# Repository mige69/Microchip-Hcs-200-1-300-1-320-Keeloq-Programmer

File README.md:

# Microchip-Hcs-200-1-300-1-320-Keeloq-Programmer

programmer keeloq hcs200/1 hcs300/1 hcs320
verified program saves hcs content on sd card
atmega644 tqfp
shield tft 2.4 mcufriends touchscreen
Keeloq simple normal secure

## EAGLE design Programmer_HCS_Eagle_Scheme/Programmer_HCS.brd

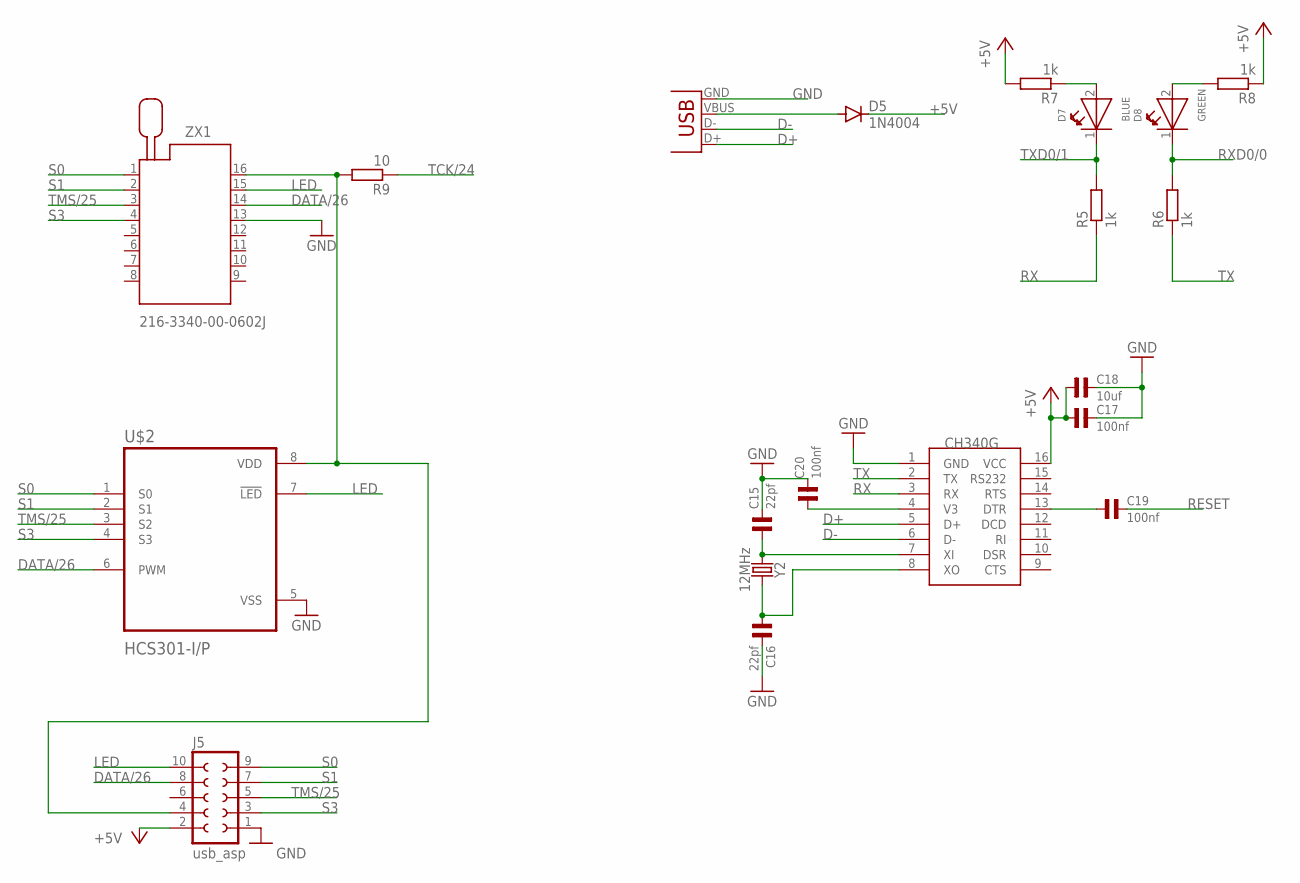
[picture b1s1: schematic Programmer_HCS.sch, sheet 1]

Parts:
C15, C16: 22pf; 0805
C17, C19, C20: 100nf; 0805
C18: 10uf; 0805
D5: 1N4004; DO214AA
D7: BLUE; 0805
D8: GREEN; 0805
J5: usb_asp; S10V
R5, R6, R7, R8: 1k; R0805
R9: 10; R0805
U$1: CH340G; SOIC16
U$2: HCS301-I/P; DIP787W46P254L927H533Q8
X1: USB-B-H
Y2: 12MHz; HC49US
ZX1: 216-3340-00-0602J

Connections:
+5V: C17.1, C18.1, D5.C, J5.2, R7.2, R8.1, U$1.16 (VCC); also elsewhere on the board
D+: U$1.5 (D+), X1.D+
D-: U$1.6 (D-), X1.D-
DATA/26: J5.8, U$2.6 (PWM), ZX1.14; also elsewhere on the board
GND: C15.2, C16.2, C17.2, C18.2, C20.2, J5.1, U$1.1 (GND), U$2.5 (VSS), X1.GND, ZX1.13; also elsewhere on the board
LED: J5.10, U$2.7 (!LED), ZX1.15
unnamed: C15.1, U$1.7 (XI), Y2.1
unnamed: C16.1, U$1.8 (XO), Y2.2
unnamed: D8.2 (A), R8.2
unnamed: D5.A, X1.VBUS
unnamed: C19.1, U$1.13 (DTR)
unnamed: D7.2 (A), R7.1
unnamed: C20.1, U$1.4 (V3)
unnamed: J5.4, R9.2, U$2.8 (VDD), ZX1.16
RESET: C19.2; also elsewhere on the board
RX: R5.1, U$1.3 (RX)
RXD0/0: D8.1 (K), R6.2; also elsewhere on the board
S0: J5.9, U$2.1 (S0), ZX1.1
S1: J5.7, U$2.2 (S1), ZX1.2
S3: J5.3, U$2.4 (S3), ZX1.4
TCK/24: R9.1; also elsewhere on the board
TMS/25: J5.5, U$2.3 (S2), ZX1.3; also elsewhere on the board
TX: R6.1, U$1.2 (TX)
TXD0/1: D7.1 (K), R5.2; also elsewhere on the board

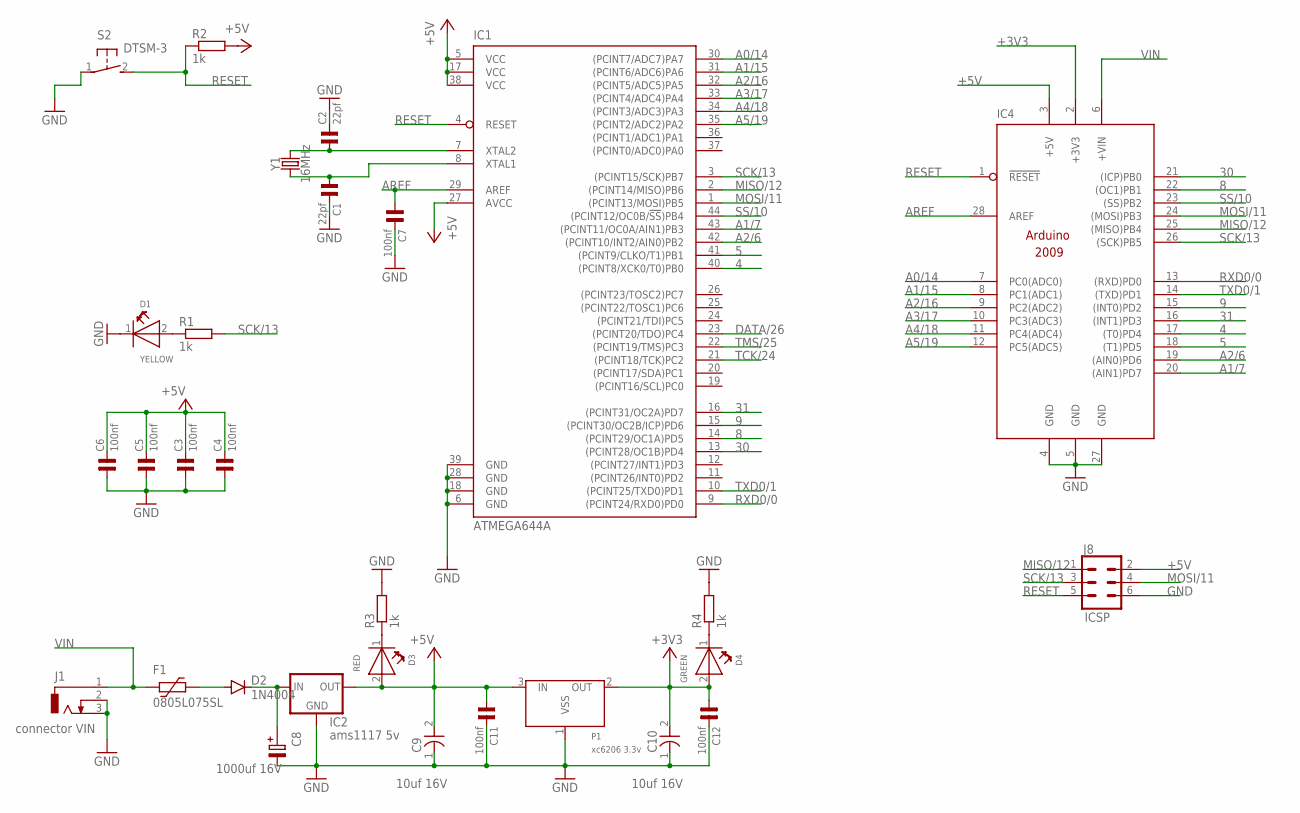
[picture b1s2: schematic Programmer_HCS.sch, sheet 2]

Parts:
C1, C2: 22pf; 0805
C3, C4, C5, C6, C7, C11, C12: 100nf; 0805
C8: 1000uf 16V; SV-G
C9, C10: 10uf 16V; 6032
D1: YELLOW; 3528-2PIN
D2: 1N4004; DO-214AC
D3: RED; 3528-2PIN
D4: GREEN; 3528-2PIN
F1: 0805L075SL; 0805L
IC1: ATMEGA644A; TQFP44
IC2: ams1117 5v; SOT223
IC4: UNO; ARDUINO2009
J1: connector VIN; DCJ0303
J8: ICSP; 2X3
P1: xc6206 3.3v; XC6206_SOT-23
R1, R2, R3, R4: 1k; R0805
S2: DTSM-3
Y1: 16MHz; HC49US

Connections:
4: IC1.40 ((PCINT8/XCK0/T0)PB0), IC4.17 ((T0)PD4)
5: IC1.41 ((PCINT9/CLKO/T1)PB1), IC4.18 ((T1)PD5)
8: IC1.14 ((PCINT29/OC1A)PD5), IC4.22 ((OC1)PB1)
9: IC1.15 ((PCINT30/OC2B/ICP)PD6), IC4.15 ((INT0)PD2)
30: IC1.13 ((PCINT28/OC1B)PD4), IC4.21 ((ICP)PB0)
31: IC1.16 ((PCINT31/OC2A)PD7), IC4.16 ((INT1)PD3)
+3V3: C10.2 (+), C12.1, D4.2 (A), IC4.2 (+3V3), P1.2 (OUT)
+5V: C3.2, C4.2, C5.2, C6.2, C9.2 (+), C11.1, D3.2 (A), IC1.5 (VCC), IC1.17 (VCC), IC1.27 (AVCC), IC1.38 (VCC), IC2.2 (OUT), IC4.3 (+5V), J8.2, P1.3 (IN), R2.2; also elsewhere on the board
A0/14: IC1.30 ((PCINT7/ADC7)PA7), IC4.7 (PC0(ADC0))
A1/7: IC1.43 ((PCINT11/OC0A/AIN1)PB3), IC4.20 ((AIN1)PD7)
A1/15: IC1.31 ((PCINT6/ADC6)PA6), IC4.8 (PC1(ADC1))
A2/6: IC1.42 ((PCINT10/INT2/AIN0)PB2), IC4.19 ((AIN0)PD6)
A2/16: IC1.32 ((PCINT5/ADC5)PA5), IC4.9 (PC2(ADC2))
A3/17: IC1.33 ((PCINT4/ADC4)PA4), IC4.10 (PC3(ADC3))
A4/18: IC1.34 ((PCINT3/ADC3)PA3), IC4.11 (PC4(ADC4))
A5/19: IC1.35 ((PCINT2/ADC2)PA2), IC4.12 (PC5(ADC5))
AREF: C7.1, IC1.29 (AREF), IC4.28 (AREF)
DATA/26: IC1.23 ((PCINT20/TDO)PC4); also elsewhere on the board
GND: C1.2, C2.2, C3.1, C4.1, C5.1, C6.1, C7.2, C8.-, C9.1 (-), C10.1 (-), C11.2, C12.2, D1.1 (K), IC1.6 (GND), IC1.18 (GND), IC1.28 (GND), IC1.39 (GND), IC2.1 (GND), IC4.4 (GND), IC4.5 (GND), IC4.27 (GND), J1.2, J1.3, J8.6, P1.1 (VSS), R3.2, R4.2, S2.1; also elsewhere on the board
MISO/12: IC1.2 ((PCINT14/MISO)PB6), IC4.25 ((MISO)PB4), J8.1
MOSI/11: IC1.1 ((PCINT13/MOSI)PB5), IC4.24 ((MOSI)PB3), J8.4
unnamed: C2.1, IC1.7 (XTAL2), Y1.2
unnamed: C1.1, IC1.8 (XTAL1), Y1.1
unnamed: D1.2 (A), R1.1
unnamed: C8.+, D2.C, IC2.3 (IN)
unnamed: D3.1 (K), R3.1
unnamed: D2.A, F1.1
unnamed: D4.1 (K), R4.1
RESET: IC1.4 (RESET), IC4.1 (!RESET), J8.5, R2.1, S2.2; also elsewhere on the board
RXD0/0: IC1.9 ((PCINT24/RXD0)PD0), IC4.13 ((RXD)PD0); also elsewhere on the board
SCK/13: IC1.3 ((PCINT15/SCK)PB7), IC4.26 ((SCK)PB5), J8.3, R1.2
SS/10: IC1.44 ((PCINT12/OC0B/!SS!)PB4), IC4.23 ((SS)PB2)
TCK/24: IC1.21 ((PCINT18/TCK)PC2); also elsewhere on the board
TMS/25: IC1.22 ((PCINT19/TMS)PC3); also elsewhere on the board
TXD0/1: IC1.10 ((PCINT25/TXD0)PD1), IC4.14 ((TXD)PD1); also elsewhere on the board
VIN: F1.2, IC4.6 (+VIN), J1.1

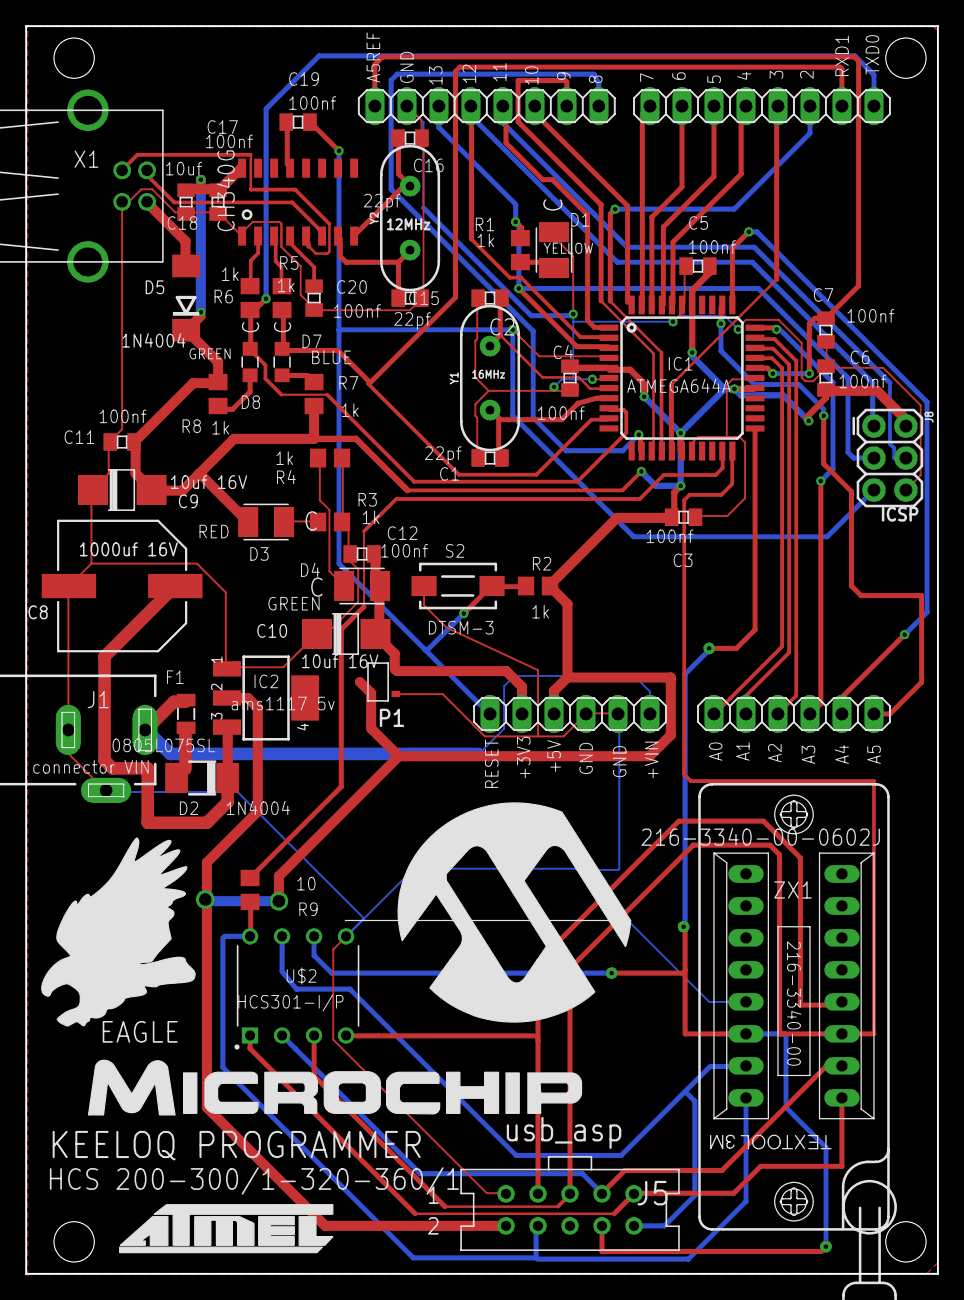
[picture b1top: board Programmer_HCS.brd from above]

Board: 2 copper layers, 72.4 x 99.1 mm, 49 parts (0 on the bottom side), 52 nets.

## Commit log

2022-01-24 Create Programmer_HCS_eagle

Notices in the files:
parts and their libraries:
cap-pan40: Copyright (C) 2004, Bob Starr
Wurth_Elektronik_Optoelectronics_rev15b: Copyright: Würth Elektronik
SparkFun-Clocks: Licensing: Creative Commons ShareAlike 4.0 International - https://creativecommons.org/licenses/by-sa/4.0
